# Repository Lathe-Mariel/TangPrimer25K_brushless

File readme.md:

# Overview
 This PCB board was made as a conversion board for Inverter Kit2 that is selling by CQ pub.
 Using this board, you can attach Tang Nano 25K(Sipeed) as an alternative to NUCLEO.
 There's Garber data made by KiCAD.

# BoM
型名 | アイテム（Item）|個数（Quantity）
---|---|---
　| 1608チップコンデンサ1μF | 1
　| 1608チップコンデンサ10μF | 1
　| 1608チップ抵抗220Ω | 8
　| 1608チップ抵抗4.7kΩ | 3
　| 1608チップ抵抗60.4Ω | 2
　| ダブルピンヘッダ（2x19列） | 2
　| JTAG用シングルピンヘッダ（1x4列） | 1
　| ジャンパ用シングルピンヘッダ（1x3列） | 1
　| RJ45ジャック | 1
TJA1441AT | CANトランシーバ | 1
SDCW3216-2-222TF | コモンモードチョークコイル | 1
SM24CANB-02HTG | | 1
TVGP01-G73BB with Gray cap | スイッチ | 2 
MCP3008-I/P | A-Dコンバータ | 1
2MS1-T1-B4-M2-Q-E | トグルスイッチ | 3
BP5293-50 | 5VDCDCコンバータ | 1

# FPGA Design
There's a sample project in sample directory.  
The project is files for Gowin EDA which is IDE for Gowin FPGA.
You can download Gowin EDA without any cost.

# Schematics

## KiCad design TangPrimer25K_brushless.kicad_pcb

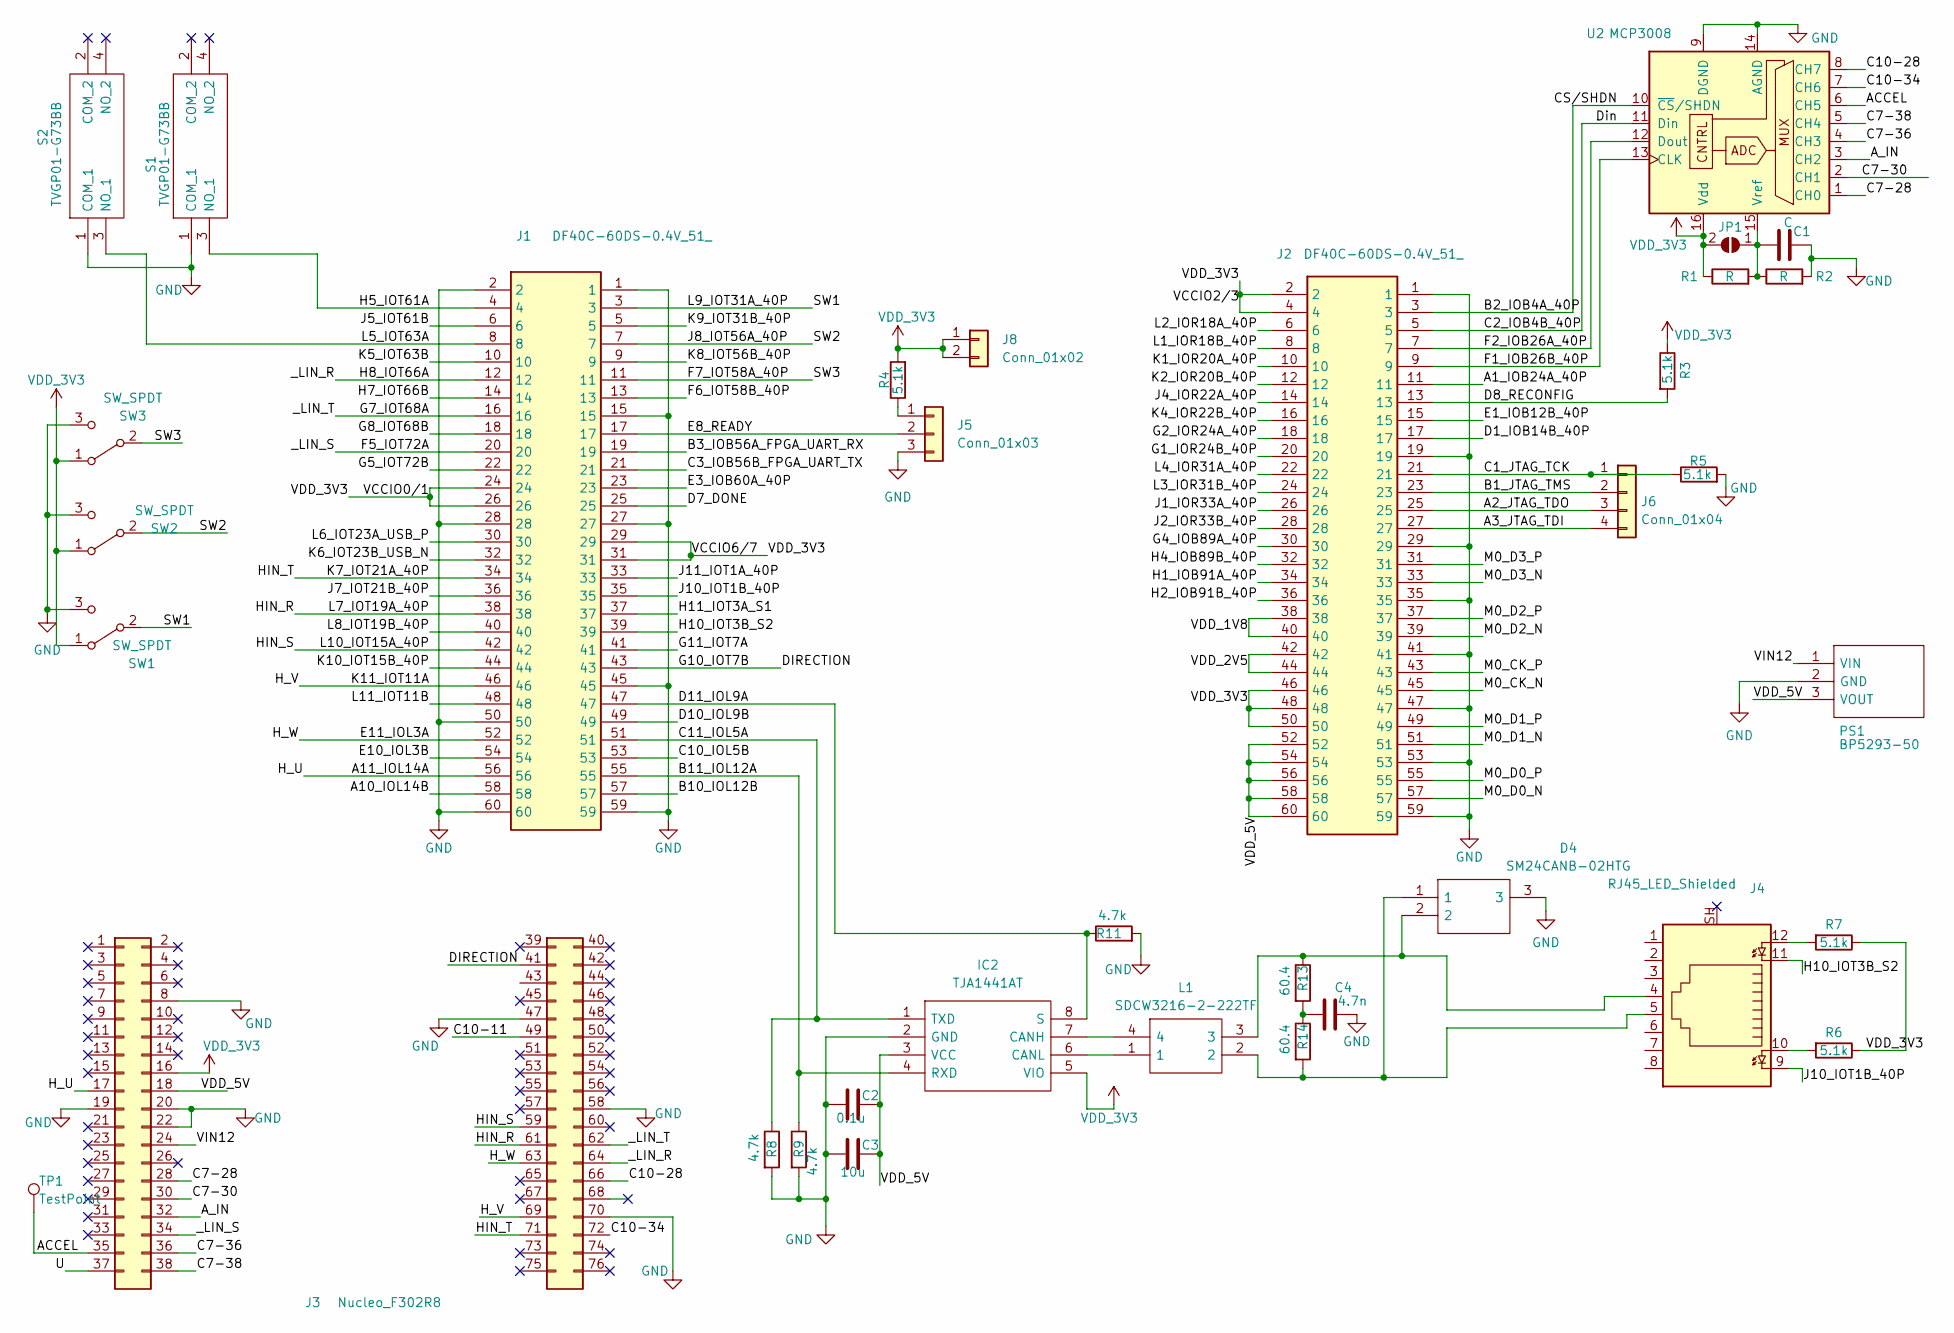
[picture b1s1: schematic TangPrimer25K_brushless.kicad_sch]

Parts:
C1: C; C_0603_1608Metric_Pad1.08x0.95mm_HandSolder
C2: 0.1u; C_0603_1608Metric_Pad1.08x0.95mm_HandSolder
C3: 10u; C_0603_1608Metric_Pad1.08x0.95mm_HandSolder
C4: 4.7n; C_0603_1608Metric_Pad1.08x0.95mm_HandSolder
D4: SM24CANB-02HTG; SM24CANB02HTG; Manufacturer_Part_Number SM24CANB-02HTG
IC2: TJA1441AT; SOIC127P600X175-8N; Manufacturer_Part_Number TJA1441AT
J1, J2: DF40C-60DS-0.4V_51_; Manufacturer_Part_Number DF40C-60DP-0.4V(51)
J3: Nucleo_F302R8; Nucleo
J4: RJ45_LED_Shielded; RJ45_Amphenol_RJHSE538X
J5: Conn_01x03; PinHeader_1x03_P2.54mm_Vertical
J6: Conn_01x04; PinHeader_1x04_P2.54mm_Vertical
J8: Conn_01x02; PinHeader_1x02_P2.54mm_Vertical
JP1: SolderJumper_2_Open; SolderJumper-2_P1.3mm_Open_TrianglePad1.0x1.5mm
L1: SDCW3216-2-222TF; SDCW32162222TF; Manufacturer_Part_Number SDCW3216-2-222TF
PS1: BP5293-50; TO254P570X1700X1780-3P; Manufacturer_Part_Number BP5293-50
R1, R2: R; R_0603_1608Metric_Pad0.98x0.95mm_HandSolder
R3, R4, R5, R6, R7: 5.1k; R_0603_1608Metric_Pad0.98x0.95mm_HandSolder
R8, R9, R11: 4.7k; R_0603_1608Metric_Pad0.98x0.95mm_HandSolder
R13, R14: 60.4; R_0603_1608Metric_Pad0.98x0.95mm_HandSolder
S1, S2: TVGP01-G73BB; TVGP01G73BB; Manufacturer_Part_Number TVGP01-G73BB
SW1, SW2, SW3: SW_SPDT; PinHeader_1x03_P2.54mm_Vertical
TP1: TestPoint; TestPoint_Pad_D1.5mm
U2: MCP3008; DIP-16_W7.62mm

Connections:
/A1_IOB24A_40P: J2.11
/A2_JTAG_TDO: J2.25, J6.3
/A3_JTAG_TDI: J2.27, J6.4
/A10_IOL14B: J1.58
/A11_IOL14A: J1.56, J3.17
/ACCEL: J3.35, TP1.1, U2.6 (CH5)
/A_IN: J3.32, U2.3 (CH2)
/B1_JTAG_TMS: J2.23, J6.2
/B2_IOB4A_40P: J2.3, U2.10 (~CS/SHDN)
/B3_IOB56A_FPGA_UART_RX: J1.19
/B10_IOL12B: J1.57
/B11_IOL12A: IC2.4 (RXD), J1.55, R9.1
/C1_JTAG_TCK: J2.21, J6.1, R5.1
/C2_IOB4B_40P: J2.5, U2.11 (Din)
/C3_IOB56B_FPGA_UART_TX: J1.21
/C7-28: J3.28, U2.1 (CH0)
/C7-30: J3.30, U2.2 (CH1)
/C7-36: J3.36, U2.4 (CH3)
/C7-38: J3.38, U2.5 (CH4)
/C10-11: J3.49
/C10-28: J3.66, U2.8 (CH7)
/C10-34: J3.72, U2.7 (CH6)
/C10_IOL5B: J1.53
/C11_IOL5A: IC2.1 (TXD), J1.51, R8.1
/D1_IOB14B_40P: J2.17
/D7_DONE: J1.25
/D8_RECONFIG: J2.13, R3.2
/D10_IOL9B: J1.49
/D11_IOL9A: IC2.8 (S), J1.47, R11.1
/DIRECTION: J1.43, J3.41
/E1_IOB12B_40P: J2.15
/E3_IOB60A_40P: J1.23
/E8_READY: J1.17, J5.2
/E10_IOL3B: J1.54
/E11_IOL3A: J1.52, J3.63
/F1_IOB26B_40P: J2.9, U2.13 (CLK)
/F2_IOB26A_40P: J2.7, U2.12 (Dout)
/F5_IOT72A: J1.20, J3.34
/F6_IOT58B_40P: J1.13
/F7_IOT58A_40P: J1.11, SW3.2 (B)
/G1_IOR24B_40P: J2.20
/G2_IOR24A_40P: J2.18
/G4_IOB89A_40P: J2.30
/G5_IOT72B: J1.22
/G7_IOT68A: J1.16, J3.62
/G8_IOT68B: J1.18
/G11_IOT7A: J1.41
/H1_IOB91A_40P: J2.34
/H2_IOB91B_40P: J2.36
/H4_IOB89B_40P: J2.32
/H5_IOT61A: J1.4, S1.3 (NO_1)
/H7_IOT66B: J1.14
/H8_IOT66A: J1.12, J3.64
/H10_IOT3B_S2: J1.39, J4.11
/H11_IOT3A_S1: J1.37
/HIN_R: J1.38, J3.61
/HIN_S: J1.42, J3.59
/HIN_T: J1.34, J3.71
/H_V: J1.46, J3.69
/J1_IOR33A_40P: J2.26
/J2_IOR33B_40P: J2.28
/J4_IOR22A_40P: J2.14
/J5_IOT61B: J1.6
/J7_IOT21B_40P: J1.36
/J8_IOT56A_40P: J1.7, SW2.2 (B)
/J10_IOT1B_40P: J1.35, J4.9
/J11_IOT1A_40P: J1.33
/K1_IOR20A_40P: J2.10
/K2_IOR20B_40P: J2.12
/K4_IOR22B_40P: J2.16
/K5_IOT63B: J1.10
/K6_IOT23B_USB_N: J1.32
/K8_IOT56B_40P: J1.9
/K9_IOT31B_40P: J1.5
/K10_IOT15B_40P: J1.44
/L1_IOR18B_40P: J2.8
/L2_IOR18A_40P: J2.6
/L3_IOR31B_40P: J2.24
/L4_IOR31A_40P: J2.22
/L5_IOT63A: J1.8, S2.3 (NO_1)
/L6_IOT23A_USB_P: J1.30
/L8_IOT19B_40P: J1.40
/L9_IOT31A_40P: J1.3, SW1.2 (B)
/L11_IOT11B: J1.48
/M0_CK_N: J2.45
/M0_CK_P: J2.43
/M0_D0_N: J2.57
/M0_D0_P: J2.55
/M0_D1_N: J2.51
/M0_D1_P: J2.49
/M0_D2_N: J2.39
/M0_D2_P: J2.37
/M0_D3_N: J2.33
/M0_D3_P: J2.31
/U: J3.37
/VDD_1V8: J2.38, J2.40
/VDD_2V5: J2.42, J2.44
/VDD_5V: C2.2, C3.2, IC2.3 (VCC), J2.52, J2.54, J2.56, J2.58, J2.60, J3.18, PS1.3 (VOUT)
/VIN12: J3.24, PS1.1 (VIN)
GND: C1.2, C2.1, C3.1, C4.2, D4.3, IC2.2 (GND), J1.1, J1.2, J1.15, J1.27, J1.28, J1.45, J1.50, J1.59, J1.60, J2.1, J2.19, J2.29, J2.35, J2.41, J2.47, J2.53, J2.59, J3.8, J3.19, J3.20, J3.22, J3.47, J3.58, J3.70, J5.3, PS1.2 (GND), R2.2, R5.2, R8.2, R9.2, R11.2, S1.1 (COM_1), S2.1 (COM_1), SW1.3 (C), SW2.3 (C), SW3.3 (C), U2.9 (DGND), U2.14 (AGND)
unnamed: C4.1, R13.2, R14.1
unnamed: D4.1, J4.5, L1.2, R14.2
unnamed: D4.2, J4.4, L1.3, R13.1
unnamed: IC2.7 (CANH), L1.4
unnamed: IC2.6 (CANL), L1.1
unnamed: J4.10, R6.2
unnamed: J4.12, R7.2
unnamed: J5.1, R4.1
unnamed: C1.1, JP1.1 (A), R1.2, R2.1, U2.15 (Vref)
VDD_3V3: IC2.5 (VIO), J1.24, J1.26, J1.29, J1.31, J2.2, J2.4, J2.46, J2.48, J2.50, J3.16, J8.1, J8.2, JP1.2 (B), R1.1, R3.1, R4.2, R6.1, R7.1, SW1.1 (A), SW2.1 (A), SW3.1 (A), U2.16 (Vdd)

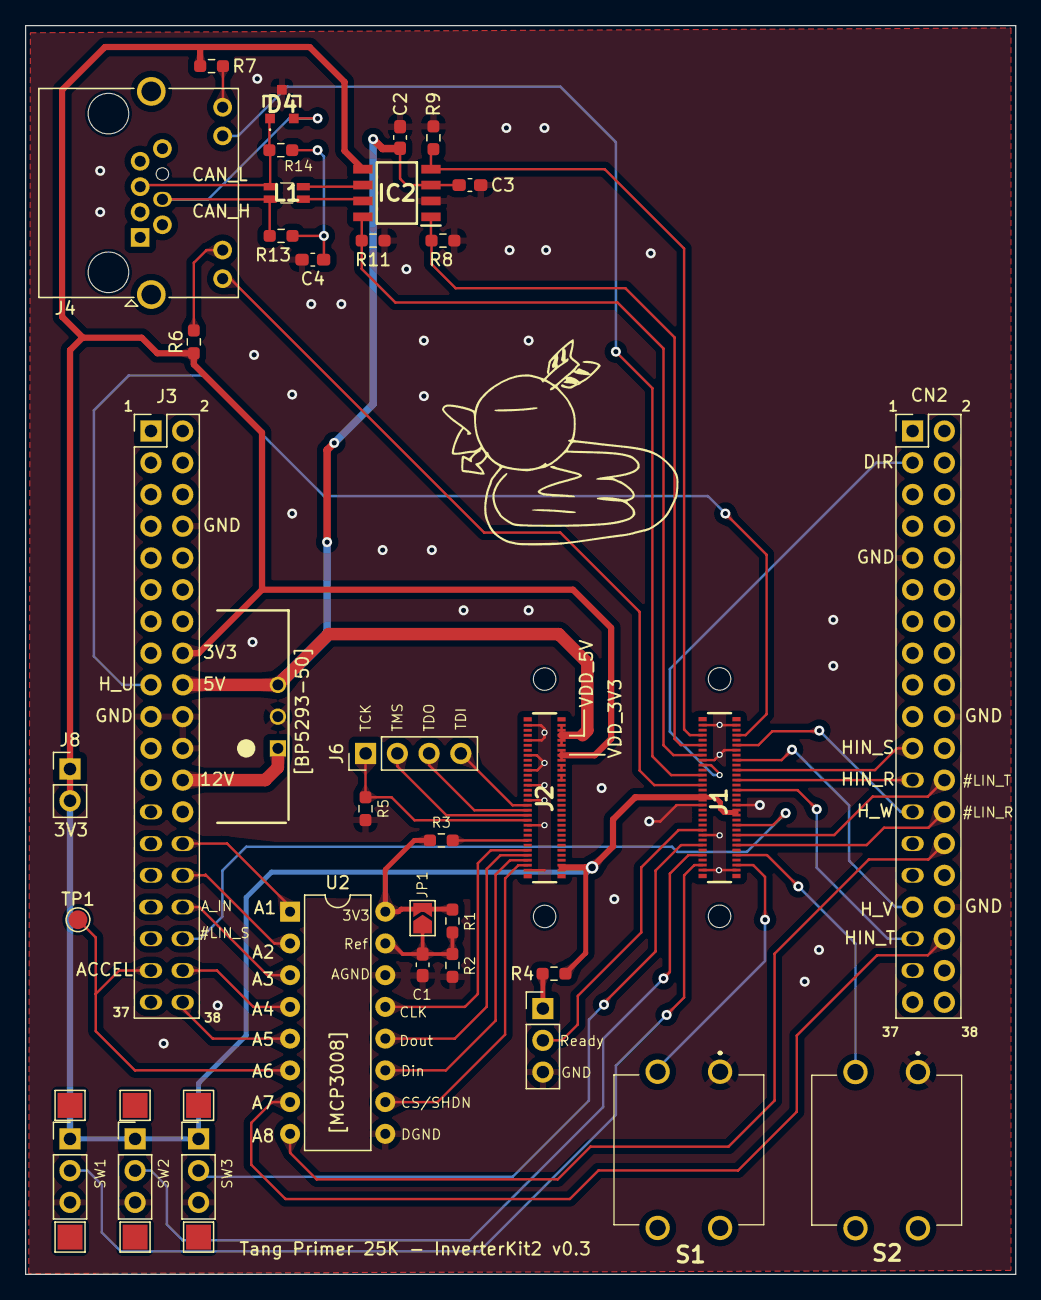
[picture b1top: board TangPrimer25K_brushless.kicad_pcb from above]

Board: 2 copper layers, 79.2 x 99.9 mm, 35 parts (0 on the bottom side), 53 nets.

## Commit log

2024-04-15 0415
2024-04-15 0416
2024-04-17 0417
2024-04-18 0418
2024-04-18 0419
2024-04-21 0421
2024-04-22 0422
2024-04-22 0423
2024-04-30 reset2
2024-04-30 test
2024-05-08 0508
2024-05-08 0509
2024-05-09 0510
2024-05-10 0511
2024-05-17 0517
2024-05-24 can design add
2024-05-24 0525
2024-05-25 0526
2024-05-29 0530
2024-06-01 0601
2024-06-03 0603
2024-06-06 0606
2024-06-06 0607
2024-06-07 0608
2024-06-09 0609
2024-06-10 0610
2024-08-14 0814
2024-08-15 0815
2024-08-28 0829
2024-09-05 0905
2024-09-10 0911
2024-09-12 0912
2024-10-02 1002
2024-10-07 1007
2024-10-08 1008
2024-10-10 1010
2024-10-23 1023
2024-12-06 1207
2025-09-10 adding function advance angle controll
2025-09-10 advanced angle
2025-09-13 advance agngle
2025-09-13 advance angle control
2025-09-14 advance angle
2025-09-14 0914
2025-09-17 0917
2025-09-19 0919
2025-09-25 0925
2025-09-25 start parameter
2025-10-12 1012
2025-10-12 1013
2025-10-13 counter_per_cycle
2025-10-20 1020
2025-10-21 slowstart
2025-10-21 advance degree adjustment
